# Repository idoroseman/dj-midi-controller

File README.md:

# dj-midi-controller

this is a project to build a dj style controller for use with SDR-Console softare used by ham radio operators

## data files
there are three folders :
- eagle for the pcb design
- arduino for the firmware
- 3d for the encloser

## sdr-console configuration
you can open the midi settings and set each fucntion as you like, or use [my presets](doc/SDR-MidiDefns_000.xml)

## Button Functions

encoder 1 is the frequency tuning

if you press button 2 (the odd shaped one) it will tune at 10x speed

encoder 2 is not currently used 

encoder 3 is volume control, if you press it - it will mute the reciever

button 1 toggles RX/TX

if you want to change button2 to a normal seperate function, check the arduino code

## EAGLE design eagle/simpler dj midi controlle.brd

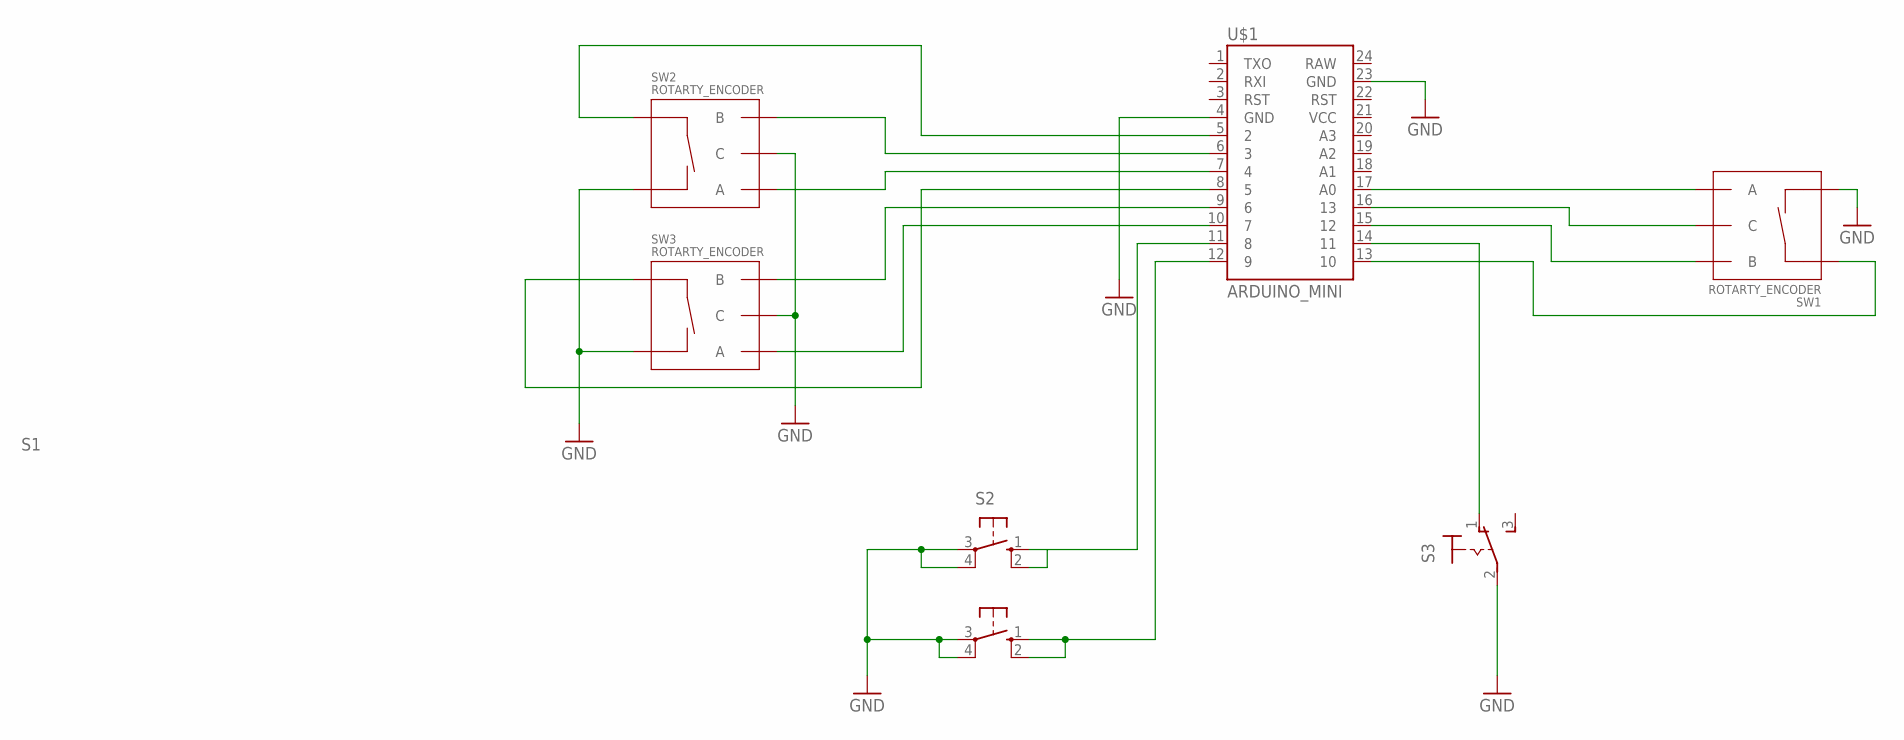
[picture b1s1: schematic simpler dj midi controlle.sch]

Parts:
S1, S2: 10-XX; B3F-10XX
S3: 320-916
SW1, SW2, SW3: ROTARTY_ENCODER; ROTARY_ENC_PLAIN
U$1: ARDUINO_MINI

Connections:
GND: S1.3, S1.4 (P1), S2.3, S2.4 (P1), S3.2, SW1.SW-, SW2.C, SW2.SW-, SW3.C, SW3.SW-, U$1.4 (GND), U$1.23 (GND)
unnamed: SW1.A, U$1.17 (A0)
unnamed: SW1.SW+, U$1.13 (10)
unnamed: SW2.B, U$1.6 (3)
unnamed: SW1.C, U$1.16 (13)
unnamed: SW1.B, U$1.15 (12)
unnamed: SW2.A, U$1.7 (4)
unnamed: SW3.B, U$1.9 (6)
unnamed: SW3.A, U$1.10 (7)
unnamed: S1.1 (S), S1.2 (S1), U$1.12 (9)
unnamed: S3.1 (O), U$1.14 (11)
unnamed: SW3.SW+, U$1.8 (5)
unnamed: S2.1 (S), S2.2 (S1), U$1.11 (8)
unnamed: SW2.SW+, U$1.5 (2)

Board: 2 copper layers, 7 parts (0 on the bottom side), 14 nets, no tracks yet.

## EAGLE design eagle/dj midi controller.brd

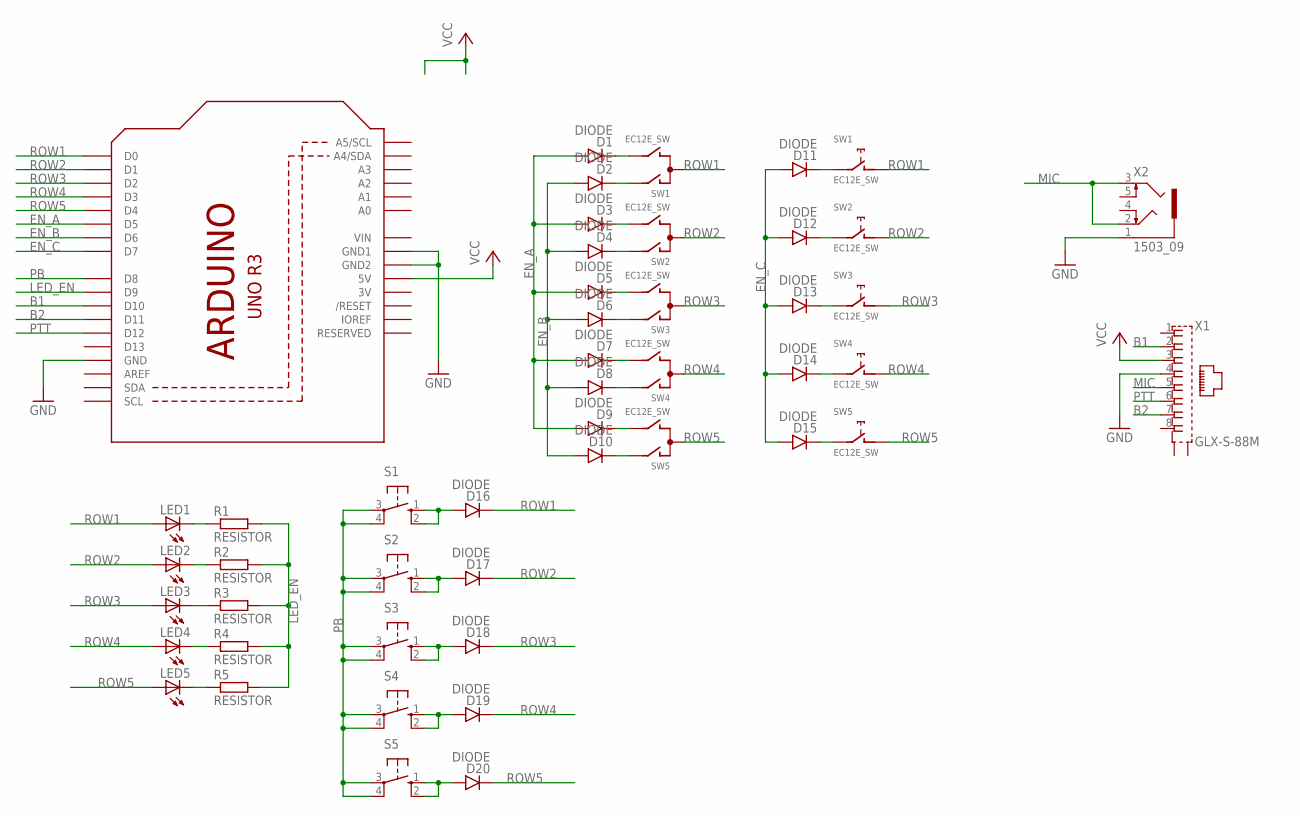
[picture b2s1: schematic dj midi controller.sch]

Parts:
D1, D2, D3, D4, D5, D6, D7, D8, D9, D10, D11, D12, D13, D14, D15, D16, D17, D18, D19, D20: DIODE; M0805
LED1, LED2, LED3, LED4, LED5: LED3MM
R1, R2, R3, R4, R5: RESISTOR; M0805
S1, S2, S3, S4, S5: 10-XX; B3F-10XX
SW1, SW2, SW3, SW4, SW5: EC12E_SW; ALPS_EC12E_SW
U2: ARDUINOR3-DIMENSION; ARDUINOR3
X1: GLX-S-88M
X2: 1503_09

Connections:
3V: U2.3V
B1: U2.D10, X1.2
B2: U2.D11, X1.7
EN_A: D1.1 (A), D3.1 (A), D5.1 (A), D7.1 (A), D9.1 (A), U2.D5
EN_B: D2.1 (A), D4.1 (A), D6.1 (A), D8.1 (A), D10.1 (A), U2.D6
EN_C: D11.1 (A), D12.1 (A), D13.1 (A), D14.1 (A), D15.1 (A), U2.D7
GND: U2.GND, U2.GND1, U2.GND2, X1.4, X2.1
LED_EN: R1.2, R2.2, R3.2, R4.2, R5.2, U2.D9
MIC: X1.5, X2.2, X2.3
unnamed: D1.2 (C), SW1.B
unnamed: D2.2 (C), SW1.A
unnamed: D3.2 (C), SW2.B
unnamed: D4.2 (C), SW2.A
unnamed: D5.2 (C), SW3.B
unnamed: D6.2 (C), SW3.A
unnamed: D7.2 (C), SW4.B
unnamed: D8.2 (C), SW4.A
unnamed: D9.2 (C), SW5.B
unnamed: D10.2 (C), SW5.A
unnamed: D16.1 (A), S1.1 (S), S1.2 (S1)
unnamed: D17.1 (A), S2.1 (S), S2.2 (S1)
unnamed: D18.1 (A), S3.1 (S), S3.2 (S1)
unnamed: D19.1 (A), S4.1 (S), S4.2 (S1)
unnamed: D20.1 (A), S5.1 (S), S5.2 (S1)
unnamed: D11.2 (C), SW1.E (2)
unnamed: D12.2 (C), SW2.E (2)
unnamed: D13.2 (C), SW3.E (2)
unnamed: D14.2 (C), SW4.E (2)
unnamed: D15.2 (C), SW5.E (2)
unnamed: LED1.K (C), R1.1
unnamed: LED2.K (C), R2.1
unnamed: LED3.K (C), R3.1
unnamed: LED4.K (C), R4.1
unnamed: LED5.K (C), R5.1
PB: S1.3, S1.4 (P1), S2.3, S2.4 (P1), S3.3, S3.4 (P1), S4.3, S4.4 (P1), S5.3, S5.4 (P1), U2.D8
PTT: U2.D12, X1.6
ROW1: D16.2 (C), LED1.A, SW1.C, SW1.D (1), U2.D0
ROW2: D17.2 (C), LED2.A, SW2.C, SW2.D (1), U2.D1
ROW3: D18.2 (C), LED3.A, SW3.C, SW3.D (1), U2.D2
ROW4: D19.2 (C), LED4.A, SW4.C, SW4.D (1), U2.D3
ROW5: D20.2 (C), LED5.A, SW5.C, SW5.D (1), U2.D4
VCC: U2.5V, X1.3
VIN: U2.VIN

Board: 2 copper layers, 43 parts (26 on the bottom side), 41 nets, no tracks yet.

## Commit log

2020-03-29 first draft
2020-03-29 added readme
2020-07-16 simplier design
2020-07-16 added some documentation
2020-07-16 fixed typos
2020-07-16 added photos
2020-07-18 added sdr console xml configuration
2020-12-26 added switch for receiver 1/2 select
2020-12-26 modified documentation
2021-03-16 better plastic cover

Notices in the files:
parts and their libraries:
SparkFun-Electromechanical: Licensing: Creative Commons ShareAlike 4.0 International - https://creativecommons.org/licenses/by-sa/4.0
